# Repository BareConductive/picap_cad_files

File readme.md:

# Bare Conductive Pi Cap CAD files

These are the CAD files for the [Pi Cap](http://www.bareconductive.com/shop/pi-cap/).

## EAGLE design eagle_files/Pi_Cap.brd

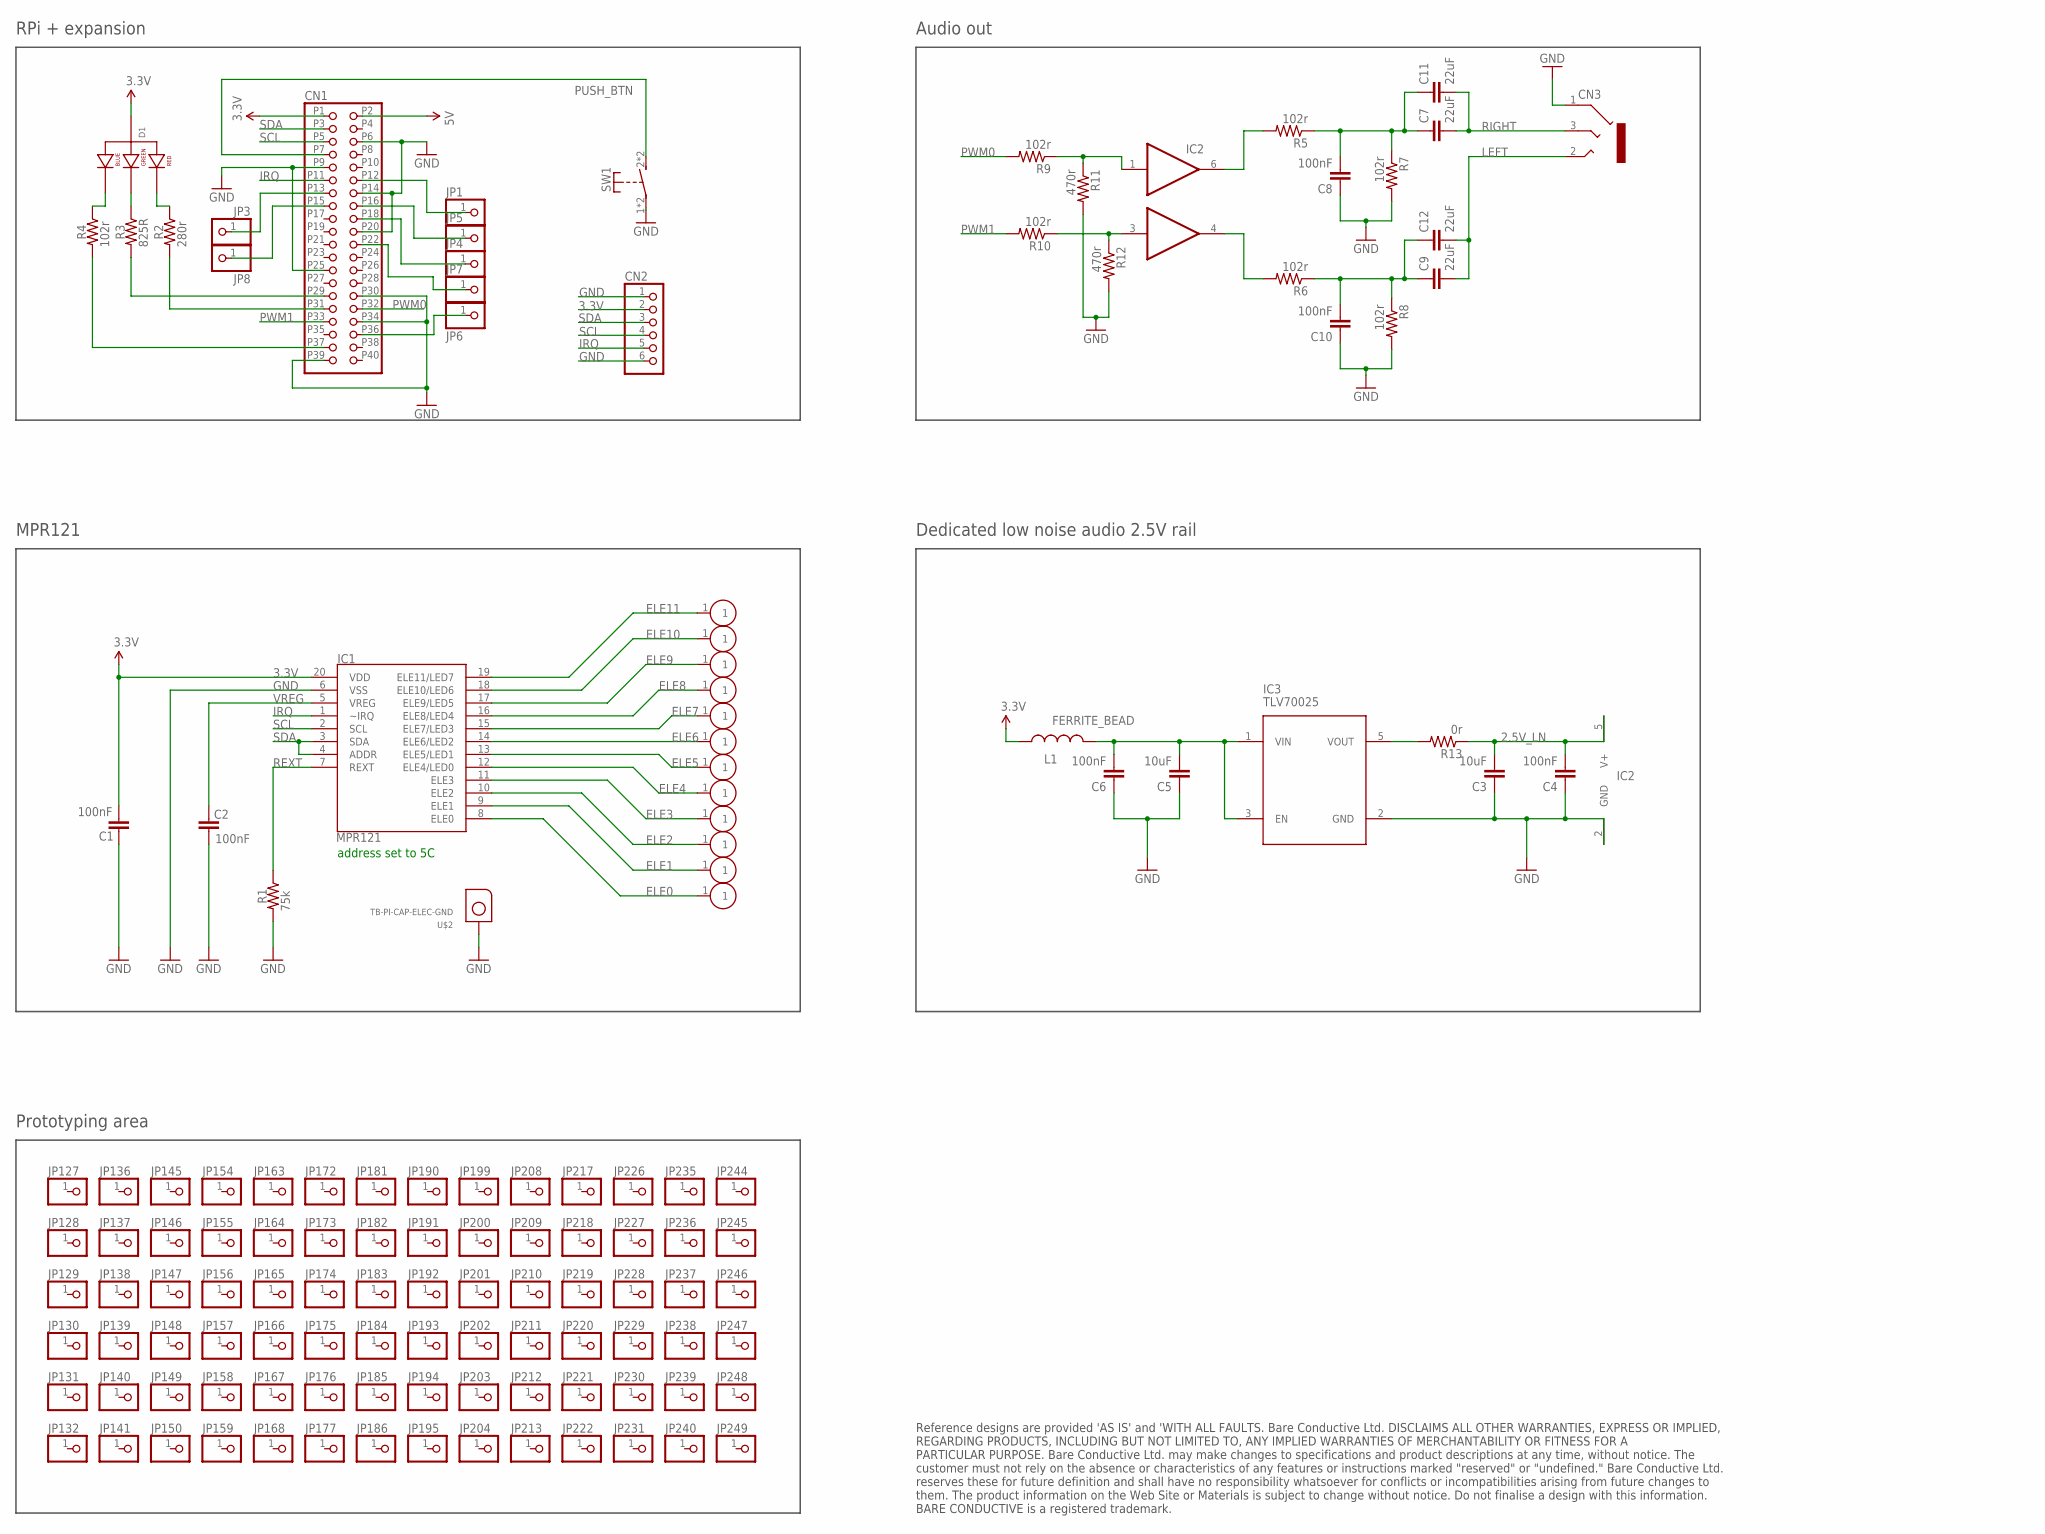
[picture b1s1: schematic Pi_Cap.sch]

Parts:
C1, C2, C4, C6, C8, C10: 100nF; 0402-CAP
C3, C5: 10uF; 1206
C7, C9, C11, C12: 22uF; 1206
CN1: PINHD-2X20/2X20_SMD; 2X20_SMD
CN2: 6W_0.5MM_FFC_RA_SMD
CN3: STEREO_SOCKET; SMD_STEREO_SOCKET
D1: PLCC4_RGB_LED; LED-3528
IC1: MPR121; QFN-20-0.4MM
IC2: DUAL_BUFFER; SOT-363
IC3: TLV70025; SC70
JP1, JP3, JP4, JP5, JP6, JP7, JP8, JP127, JP128, JP129, JP130, JP131, JP132, JP136, JP137, JP138, JP139, JP140, JP141, JP145, JP146, JP147, JP148, JP149, JP150, JP154, JP155, JP156, JP157, JP158, JP159, JP163, JP164, JP165, JP166, JP167, JP168, JP172, JP173, JP174, JP175, JP176, JP177, JP181, JP182, JP183, JP184, JP185, JP186, JP190, JP191, JP192, JP193, JP194, JP195, JP199, JP200, JP201, JP202, JP203, JP204, JP208, JP209, JP210, JP211, JP212, JP213, JP217, JP218, JP219, JP220, JP221, JP222, JP226, JP227, JP228, JP229, JP230, JP231, JP235, JP236, JP237, JP238, JP239, JP240, JP244, JP245, JP246, JP247, JP248, JP249: PINHD-1X1CB; 1X01-CLEANBIG
L1: FERRITE_BEAD; C0402
R1: 75k; 0402-RES
R2: 280r; 0402-RES
R3: 825R; 0402-RES
R4, R5, R6, R7, R8, R9, R10: 102r; 0402-RES
R11, R12: 470r; 0402-RES
R13: 0r; 0402-RES
SW1: SMD_RA_PUSH_SW
U$1: EDGE-ELEC-LEFT
U$2: TB-PI-CAP-ELEC-GND
U$3: EDGE-ELEC-RIGHT
U$17, U$18, U$22, U$24, U$26, U$27, U$28, U$29, U$30, U$31: EDGE-ELEC

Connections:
2.5V_LN: C3.2, C4.2, IC2.5 (V+), R13.1
3.3V: C1.1, CN1.P1 (1), CN2.2, D1.1 (ANODE), IC1.20 (VDD), L1.1
5V: CN1.P2 (2)
ELE0: IC1.8 (ELE0), U$1.1
ELE1: IC1.9 (ELE1), U$31.1
ELE2: IC1.10 (ELE2), U$30.1
ELE3: IC1.11 (ELE3), U$29.1
ELE4: IC1.12 (ELE4/LED0), U$28.1
ELE5: IC1.13 (ELE5/LED1), U$27.1
ELE6: IC1.14 (ELE6/LED2), U$26.1
ELE7: IC1.15 (ELE7/LED3), U$24.1
ELE8: IC1.16 (ELE8/LED4), U$22.1
ELE9: IC1.17 (ELE9/LED5), U$18.1
ELE10: IC1.18 (ELE10/LED6), U$17.1
ELE11: IC1.19 (ELE11/LED7), U$3.1
GND: C1.2, C2.1, C3.1, C4.1, C5.1, C6.1, C8.1, C10.1, CN1.P6 (6), CN1.P9 (9), CN1.P14 (14), CN1.P20 (20), CN1.P25 (25), CN1.P30 (30), CN1.P34 (34), CN1.P39 (39), CN2.1, CN2.6, CN3.1, IC1.6 (VSS), IC2.2 (GND), IC3.2 (GND), R1.2, R7.2, R8.2, R11.2, R12.2, SW1.1, SW1.3, U$2.1
IRQ: CN1.P11 (11), CN2.5, IC1.1 (~IRQ)
LEFT: C9.2, C12.2, CN3.2
unnamed: D1.2 (BLUE_CATHODE), R4.1
unnamed: D1.4 (GREEN_CATHODE), R3.1
unnamed: D1.3 (RED_CATHODE), R2.1
unnamed: CN1.P31 (31), R2.2
unnamed: CN1.P29 (29), R3.2
unnamed: CN1.P13 (13), JP3.1
unnamed: CN1.P37 (37), R4.2
unnamed: CN1.P36 (36), JP6.1
unnamed: CN1.P22 (22), JP7.1
unnamed: CN1.P18 (18), JP4.1
unnamed: CN1.P16 (16), JP5.1
unnamed: IC2.1 (IN_1), R9.1, R11.1
unnamed: CN1.P12 (12), JP1.1
unnamed: IC2.6 (OUT_1), R5.2
unnamed: IC2.4 (OUT_2), R6.2
unnamed: CN1.P15 (15), JP8.1
unnamed: C7.1, C8.2, C11.1, R5.1, R7.1
unnamed: IC2.3 (IN_2), R10.1, R12.1
unnamed: C9.1, C10.2, C12.1, R6.1, R8.1
unnamed: C5.2, C6.2, IC3.1 (VIN), IC3.3 (EN), L1.2
unnamed: IC3.5 (VOUT), R13.2
PUSH_BTN: CN1.P7 (7), SW1.2 (S), SW1.4 (S)
PWM0: CN1.P32 (32), R9.2
PWM1: CN1.P33 (33), R10.2
REXT: IC1.7 (REXT), R1.1
RIGHT: C7.2, C11.2, CN3.3
SCL: CN1.P5 (5), CN2.4, IC1.2 (SCL)
SDA: CN1.P3 (3), CN2.3, IC1.3 (SDA), IC1.4 (ADDR)
VREG: C2.2, IC1.5 (VREG)

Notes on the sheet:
Reference designs are provided 'AS IS' and 'WITH ALL FAULTS. Bare Conductive Ltd. DISCLAIMS ALL OTHER WARRANTIES, EXPRESS OR IMPLIED, REGARDING PRODUCTS, INCLUDING BUT NOT LIMITED TO, ANY IMPLIED WARRANTIES OF MERCHANTABILITY OR FITNESS FOR A PARTICULAR PURPOSE. Bare Conductive Ltd. may make change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
address set to 5C
Prototyping area
MPR121
RPi + expansion
Audio out
Dedicated low noise audio 2.5V rail
IC2

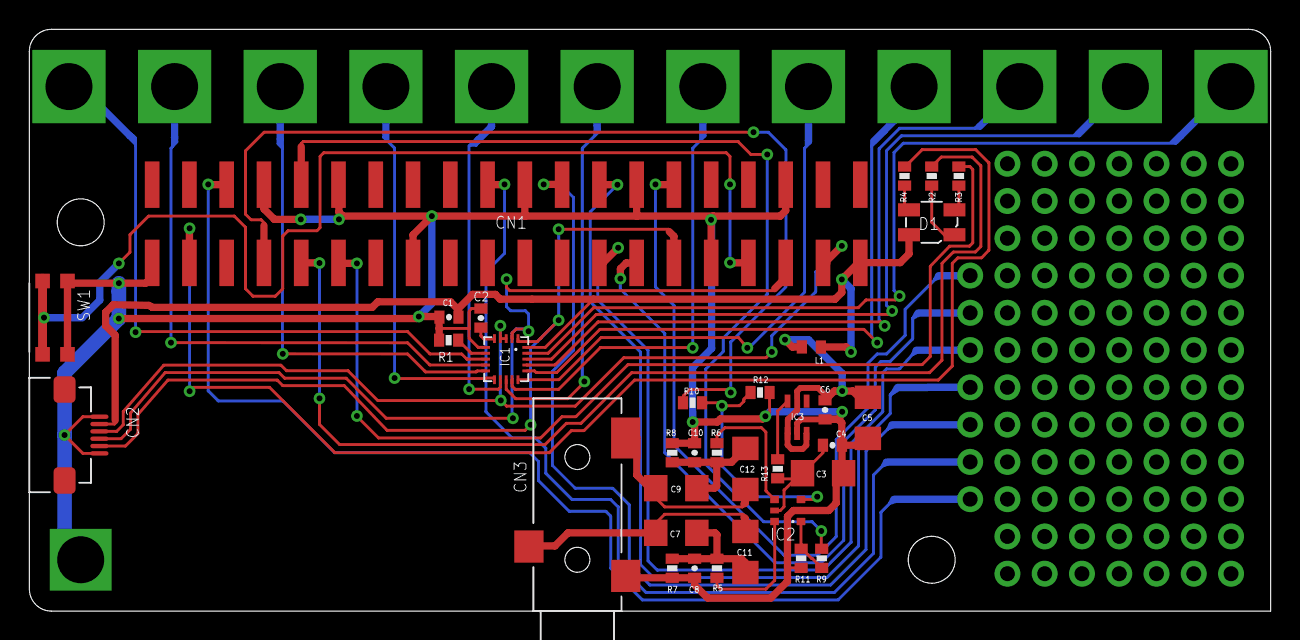
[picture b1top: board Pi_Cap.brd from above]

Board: 4 copper layers, 84.6 x 39.6 mm, 138 parts (1 on the bottom side), 46 nets.

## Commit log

2016-12-01 Init public commit

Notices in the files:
parts and their libraries:
SparkFun-Passives: Licensing: Creative Commons ShareAlike 4.0 International - https://creativecommons.org/licenses/by-sa/4.0
